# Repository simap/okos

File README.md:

One Kilobyte Operating System (OKOS)
================

Tiny OS for 1kB challenge.

Blurring the line between embedded system and general purpose computer. Inspired by all those wizardly tricks that brought computing to the masses on limited hardware.

OKOS is an operating system that allows the user to edit text or assembly source files code, assemble these into executables, and run their programs.

Features
---

* Runs on a PIC18f25k50, the MCU in the HaD SuperCon Badge!
* Display driver and API
	* Supports SSD1306 OLED display with 128x64 pixels over i2c, with the font included that is 32x8 characters.
	* Minimal 3x5 tiny font (remember original Apple ][ uppercase only font?)
	* Line buffered text drawing api (write whole row at a time)
	* Optional lowercase font, with descender support 3x5.5! But it takes 10 more bytes to support :(
	* Check out git history for a full ascii compatible font + display driver in less than 400 bytes.
* Filesystem (if you can call it that)
	* Actually just chopping 32k flash into 16 * 2k files.
	* 15 files available to user numbered 1-F. Can be either text files or programs.
* Touch keyboard
	* Chainable capacitive keyboard controller in 106.75 bytes.
	* Can scan up to 256 keys, though OKOS uses only 44 w/ 6 chained controllers.
	* Normal sized sized qwerty keyboard (keyboard and controller Eagle files included)
* Very basic command line interface lets you edit files, assemble them, and run programs
* Minimal instruction set assembler for the PIC MCU
	* What kind of OS doesn't let you write code?!?
	* Minimal, but workable, instruction set support.
	* Writes executable machine code into another file. Not interpreted!
* Visual Text Editor
	* Hopefully better than edlin
* Run
	* User program takes over
	* Core API available
	* User program interrupts supported (ISR vector depends on what program is running)
* OKOS is just ok because OKOS is just OK.

One Kilobyte Breakdown
-------

Visual Text Editor
================

Edit a text file with `e <file>` e.g. `e 1` to edit the text file `1`.

The current line will have an arrow in the left-side gutter. Arrow keys are not supported, but instead the keypad 8 (up) and 2 (down) keys are used for navigating. You can scroll through the file with these arrow keys.

The cursor is always at the end of the line. You can delete with backspace (including over newlines), or type to add more characters to a line. Pressing enter will append a newline.

Save the file with the `F1` key.

Assembler
================

Assemble a file with `a <source> <out>` e.g. `a 1 2` assembles source code in file `1` writing the executable to file `2`.

Minimal usable PIC instruction set.

3 character mnemonics to save space.

* `;` for comments, can be anywhere
* `.` on a line alone to end the file/parsing. **REQUIRED**

User ISR starts at offset **`0x04`** or. This gives you enough room to jump away at the start of your program.
Boilerplate program with an ISR:

```
bra 0012 ; jump past ISR
; insert your ISR code here
; ...
bra 000b ; execute a return
; at address 12. insert your code here
. ; EOF
```

User memory starts at address 0x3A, with the line buffer at 0x1A, anything before that is needed by the core API. If you don't use the API, feel free to reclaim this memory! Note that if you use ISRs, address 0x00 controls which file block the ISR jumps to.

Unfortunately, there wasn't enough room to support labels.

#### Instruction Set

| PIC instruction | short mnemonic | args | notes |
| --- | --- | --- | --- |
| bcf | bcf | f, b | 1 instruction |
| bsf | bsf | f, b | 1 instruction |
| btfsc | btc | f, b | 1 instruction |
| btfss | bts | f, b | 1 instruction |
| movlw | mvl | k | 1 instruction |
| movwf | mvw | f | 1 instruction |
| movf | mvf | f, d | 1 instruction |
| addwf | add | f, d | 1 instruction |
| andwf | and | f, d | 1 instruction |
| iorwf | ior | f, d | 1 instruction |
| xorwf | xor | f, d | 1 instruction |
| rlcf | rlc | f, d | 1 instruction |
| rrcf | rrc | f, d | 1 instruction |
| goto | bra | k | 2 instructions<br>target address is doubled. Think of them as instruction word addresses instead of byte addresses. File 1 starts at `0x400`|
| call | cal | k | 2 instructions. Same addressing as goto |
| return | - | - | NOT IMPLEMENTED<br>Use **`bra b`** |

**NOTE** return is not implemented, but a return instruction is placed at address 0x16 (word 0xb), jumping there will effect a return.

#### Core API

These API are available and potentially useful to user written programs.

| Routine           | address    | cal address | Notes   |
| ----------------- | ---------- | ----------- | ------- | 
| return_bra        | 0x000016   | 000B        | Use this to return. |
| oledDrawFlushLine | 0x00012c   | 0096        | write up to 32 characters to 0x1A. Filled with spaces on return. | 
| readKey           | 0x00015c   | 00AE        | Waits for keypress, returns character in WREG, also in 0x03. Blocks until key is pressed. You probably want to write something better in an ISR. |
| openFile          | 0x0002d2   | 0169        | Sets up TBLPTR for reading/writing to the given file in WREG |
| fputc             | 0x000294   | 014A        | Writes a byte in WREG, flushing pages as needed |
| flushLastPage     | 0x0002a2   | 0151        | If bit 0 in memory 0x01 is set, you need to call this once to flush the last page, since pages are only flushed by fputc in 64b increments. |

Running Programs
================

Once you've written and assembled an executable, you can run with with `r <file>` e.g. `r 2` to run file `2`.

Your program takes over until the computer is reset.

In main.asm, a define can be set to write an example program to flash. Both the assembler version and the text file are included.

Hardware
================

OKOS was written on and designed to run on the PIC MCU in the HaD SuperCon badge. The badge exposes a few GPIO, with i2c support. 

Originally OKOS was written with PS2 keyboard support, though later this was replaced with a capacitive touch keyboard so that all code could be accounted for. A define can be set to re-enable PS2 keyboard support without having to make your own keyboard hardware.

The keyboard is regular sized, and the solder joints were sanded down for a smooth surface before it was coated with polyurethane. It has a nice feel to it!

The capacitive touch keyboard is scanned with a handful of daisy chained pic16f1574 wired to a qwerty touch keyboard. Each runs exactly the same copy of code and scans 8 keys, passing messages from other controllers in the chain.

6 of these controllers chained together make up the keyboard controller. 

There is also a board for placing the OLED display and doing level shifting to support PS2 keyboards. This connects to the expansion port on the badge.

Notes
================

### Character set

Supports 0-9, a-z, period, semicolon, space, newline, esc, F1, backspace, Keypad 2,8,6

Maps directly to hex, such that 0x0 => '0', 0xa => 'A'.

### keyboard

Supports PS2 keyboards, decode scancodes into character set.

* simple protocol
* can ignore keyup. 
* ignore most special keys.

### filesystem

* pic18f25k50 has 32k flash. Split into 16 "files" of 2k each. file 0 (half of it anyway) contains OKOS.
* There wasn't enough space to do much else

### display

* the 128x64 oled needs very little setup.
* could get 10 lines of text (+ 4 pixels spare), but requires extra bit shifting. 8 lines of 8 pixels is easy w/ the displays 8 bit tall row x 128 segments.
* Each font face is 15 bits. To save space, only uppercase is supported, though the code can support lowercase and even use the 16th bit to shift down for lowercase descenders with 10 more bytes of code.
* Originally it rendered characters on the fly and send to display, but positioning and redraw was difficult. Now uses a line buffer and draws one row at a time, and is faster.

### MCU

Microchip PIC18f25k50

* uses 16-bit instruction words, and can store 2-8bit bytes per word easily.
* has 32k of flash, leaving plenty for filesystem
* Has almost enough RAM to fit entire 2k "file" into memory. 
* Also happens to be in the HaD SuperCon Badge.

### A Comment on Interrupts

First of all, I love interrupts. It's why I added some hooks that allow user programs to have ISRs at all.

However, when I went to write the i2c display stuff and the keyboard handling code, the ISR quickly consumed a lot of program space just saving and restoring registers. On top of that, the state machine, timers/timeouts, checking flags, etc. all took more space than I had.

1K Mapfile evidence
========

The main controller OS program code weighs in at 912 bytes. The keyboard controller is 106.75 bytes (61 14-bit instructions).

Main controller & OS
--------

[Full mapfile here](okos.X/dist/default/production/okos.X.production.map)

Note that configuraton fuses on the main PIC are located at `0x300000` and are not actually program flash, the programm usage calculation is flawed! Main controller program memory ends (and includes) address `0x00038f` - 912 bytes. Also `.cinit` is a bug/feature of MPLAB that could be removed with a custom linker file or by switching to absolute mode (as was done for the keyboard controller).

Here's the relevant bit from the mapfile:

```
                              Program Memory Usage 
                               Start         End      
                           ---------   ---------      
                            0x000000    0x00038f      
                            0x300000    0x300003      
                            0x300005    0x300006      
                            0x300008    0x30000d      
            924 out of 33048 program addresses used, program memory utilization is 2%
```

Keyboard controller
--------

[Full mapfile here](keyboard.X/dist/default/production/keyboard.X.production.map)

Note that configuraton fuses on the keyboard controller PIC are located at `0x008007` and are not actually program flash, the programm usage calculation is flawed! The program memory ends (and includes) address `0x00003c ` - 61 x 14-bit instructions or 854 bits = 106.75 bytes.

Here's the relevant bit from the mapfile:

```
                              Program Memory Usage 
                               Start         End      
                           ---------   ---------      
                            0x000000    0x00003c      
                            0x008007    0x008008      
            63 out of 4103 program addresses used, program memory utilization is 1%
```

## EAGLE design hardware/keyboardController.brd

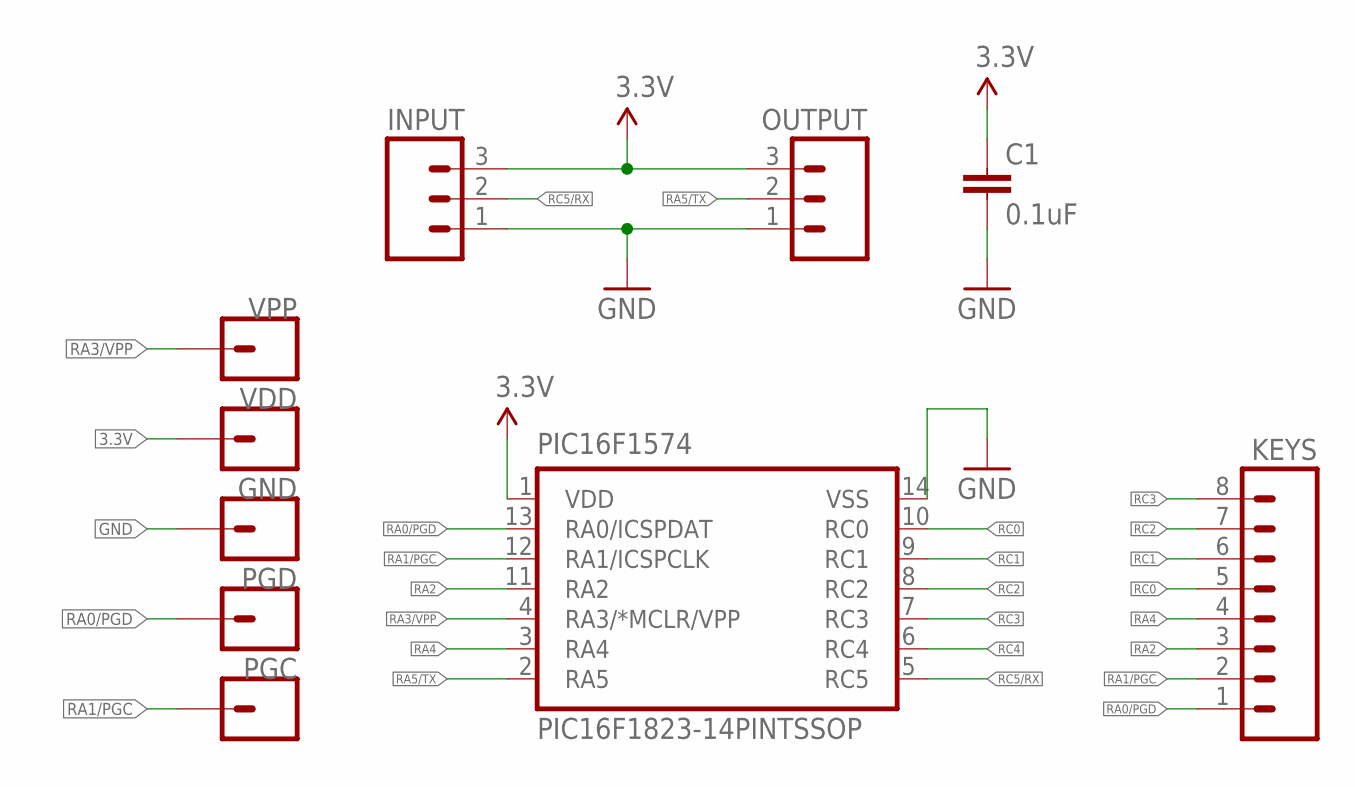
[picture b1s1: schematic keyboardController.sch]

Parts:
C1: 0.1uF; 0805
GND: M01PTH; 1X01
INPUT: M03LONGPADS; 1X03_LONGPADS
KEYS: M08LONGPADS; 1X08_LONGPADS
OUTPUT: M03LONGPADS; 1X03_LONGPADS
PGC: M01PTH; 1X01
PGD: M01PTH; 1X01
PIC16F1574: PIC16F1823-14PINTSSOP; TSSOP14
VDD: M01PTH; 1X01
VPP: M01PTH; 1X01

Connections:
3.3V: C1.1, INPUT.3, OUTPUT.3, PIC16F1574.1 (VDD), VDD.1
GND: C1.2, GND.1, INPUT.1, OUTPUT.1, PIC16F1574.14 (VSS)
RA0/PGD: KEYS.1, PGD.1, PIC16F1574.13 (RA0/ICSPDAT)
RA1/PGC: KEYS.2, PGC.1, PIC16F1574.12 (RA1/ICSPCLK)
RA2: KEYS.3, PIC16F1574.11 (RA2)
RA3/VPP: PIC16F1574.4 (RA3/*MCLR/VPP), VPP.1
RA4: KEYS.4, PIC16F1574.3 (RA4)
RA5/TX: OUTPUT.2, PIC16F1574.2 (RA5)
RC0: KEYS.5, PIC16F1574.10 (RC0)
RC1: KEYS.6, PIC16F1574.9 (RC1)
RC2: KEYS.7, PIC16F1574.8 (RC2)
RC3: KEYS.8, PIC16F1574.7 (RC3)
RC4: PIC16F1574.6 (RC4)
RC5/RX: INPUT.2, PIC16F1574.5 (RC5)

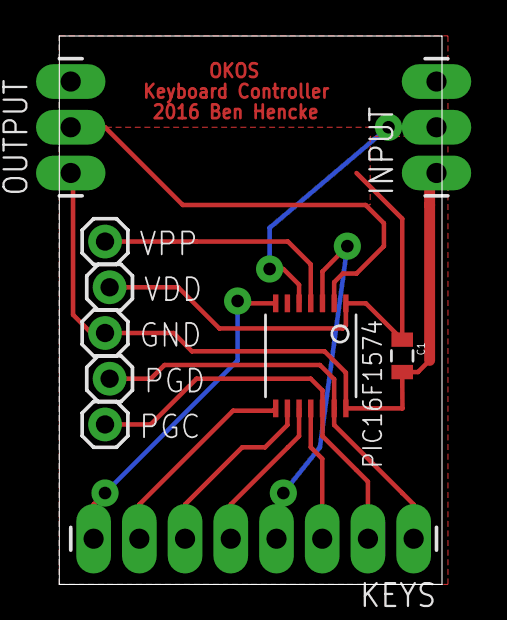
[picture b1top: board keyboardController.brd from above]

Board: 2 copper layers, 21.3 x 30.5 mm, 10 parts (0 on the bottom side), 13 nets.

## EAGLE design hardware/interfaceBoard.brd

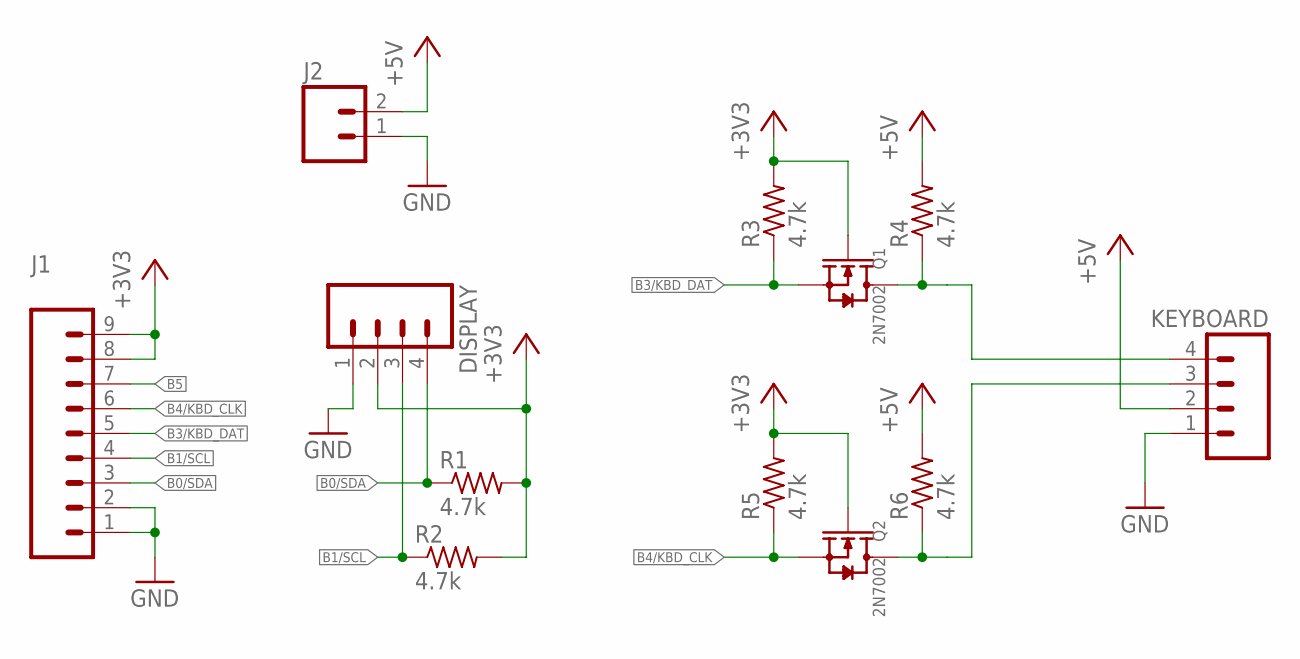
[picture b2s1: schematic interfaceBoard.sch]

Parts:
DISPLAY: M04LOCK_LONGPADS; 1X04_LOCK_LONGPADS
J1: M09LOCK-LONGPADS; 1X09_LOCK_LONGPADS
J2: M02PTH3; 1X02_LONGPADS
KEYBOARD: M04LOCK_LONGPADS; 1X04_LOCK_LONGPADS
Q1, Q2: 2N7002; SOT-23
R1, R2, R3, R4, R5, R6: 4.7k; R0805

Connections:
+3V3: DISPLAY.2, J1.8, J1.9, Q1.1 (G), Q2.1 (G), R1.2, R2.2, R3.2, R5.2
+5V: J2.2, KEYBOARD.2, R4.2, R6.2
B0/SDA: DISPLAY.4, J1.3, R1.1
B1/SCL: DISPLAY.3, J1.4, R2.1
B3/KBD_DAT: J1.5, Q1.2 (S), R3.1
B4/KBD_CLK: J1.6, Q2.2 (S), R5.1
B5: J1.7
GND: DISPLAY.1, J1.1, J1.2, J2.1, KEYBOARD.1
unnamed: KEYBOARD.4, Q1.3 (D), R4.1
unnamed: KEYBOARD.3, Q2.3 (D), R6.1

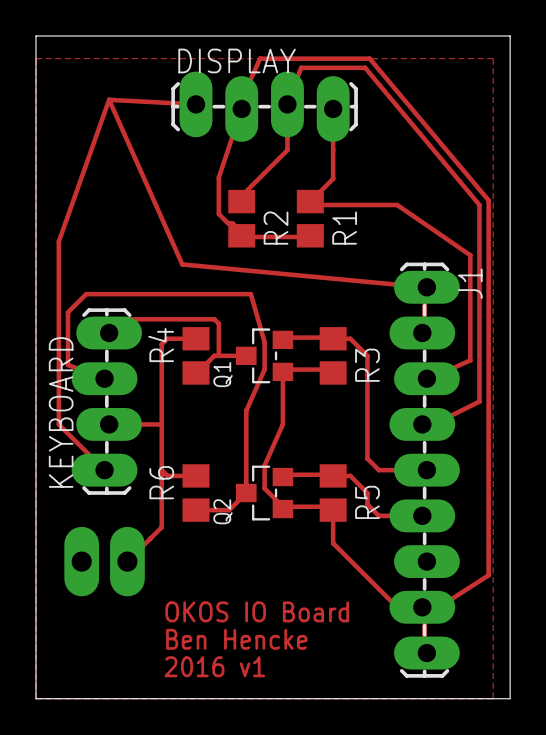
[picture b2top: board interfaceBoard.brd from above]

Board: 2 copper layers, 26.3 x 36.8 mm, 12 parts (0 on the bottom side), 9 nets.

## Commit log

2016-11-19 initial working i2c display
2016-11-19 ignore
2016-11-20 font WIP, testing buffered text display
2016-11-23 switch to row based output, add newline, tweak init code
2016-11-24 fit lowercase decender characters. still TODO support shifting down when drawing
2016-11-24 optimize
2016-11-24 indent db directive to avoid compiler warnings
2016-11-24 support descenders in font
2016-11-24 descender font support
2016-11-26 write keyboard handling code, table lookup idea
2016-11-26 fix logic reverse
2016-11-26 support drawing a cursor (or line), keep track of column
2016-11-26 pull ps2 clock low after done reading until next time
2016-11-26 vars
2016-11-27 most of editor
2016-11-27 use resetBufferFsr call
2016-11-27 move some init stuff to reset vector
2016-11-27 take tabs out until its supported
2016-11-27 more editor work
2016-11-28 file save
2016-11-28 memory
2016-11-28 insert, move up/down
2016-11-28 assembler lookup table
2016-11-28 in command mode, set cursor to eol
2016-11-28 cut upper/lowercase support, custom charset. WIP
2016-11-28 rewrite to use condensed charset
2016-11-28 remove redundant access flags
2016-11-28 include keycodes table in first bank
2016-11-28 cleanup and move all tables starting in first page
2016-11-28 removed
2016-12-01 assembler working
2016-12-01 fix charset issues, trim more init code from oled
2016-12-01 fix charset, trim code a bit. only support 0-3 command keys
2016-12-01 trim keyboard code
2016-12-01 cleanup main prog, implement user ISR handling code
2016-12-01 save 10 bytes by making eyes bleed
2016-12-01 convert strings to hacked charset. needs cleanup
2016-12-01 interface pcb
2016-12-01 lsb first, oops! also fix off by one math
2016-12-01 quick keyboard test
2016-12-01 computed GOTO was breaking in debugger, read PCL to prime PCLAT
2016-12-02 readme work
2016-12-04 typo
2016-12-04 editor can view files, scroll around WIP. switch up keyboard codes a bit
2016-12-04 working editor, switch write method to use buffered line
    this saves code, and is faster. no start+stop per character
2016-12-04 updated testkeyboard for new api
2016-12-04 save an instruction
2016-12-04 save 1 instruction
2016-12-05 wrong call, want to suppress output
2016-12-05 it works! map file shows 1022 bytes
    took out the clock hold on keyboard
    fixed some memory pointer issues
    even with 2 lost for cinit
2016-12-05 docs
2016-12-05 oops, only reserve 32 for line, not 0x32
2016-12-05 more readme
2016-12-05 dont overwrite "files" when programming
2016-12-05 small edits
2016-12-05 add bit about hardware
2016-12-05 tdypo
2016-12-05 more text
2016-12-05 oops, fix run bug, free up more space!
2016-12-05 fix newline conversion
2016-12-07 comment about loop, remove old stop
2016-12-07 comment about interrupts
2016-12-20 add okos keyboard code and boards
2016-12-20 example files (WIP)
2016-12-21 update okos to use touch keyboard
2016-12-21 unused file
2016-12-21 cleanup, comments, remove unused oledCol
2016-12-21 update readme with mapfile info, and touch keyboard
2016-12-21 adding mapfiles as supporting evidence
2016-12-21 link to mapfiles

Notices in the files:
parts and their libraries:
SparkFun-Connectors: Licensing: Creative Commons ShareAlike 4.0 International - https://creativecommons.org/licenses/by-sa/4.0
